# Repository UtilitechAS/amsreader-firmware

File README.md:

# AMS Reader
This code is designed to decode data from electric smart meters installed in many countries in Europe these days. The data is presented in a graphical web interface and can also send the data to a MQTT broker which makes it suitable for home automation project. Originally it was only designed to work with Norwegian meters, but has since been adapter to read any IEC-62056-7-5 or IEC-62056-21 compliant meters.

Later development have added Energy usage graph for both day and month, as well as future energy price. The code can run on any ESP8266 or ESP32 hardware which you can read more about in the [Wiki](https://wiki.amsleser.no/). If you don't have the knowledge to set up a ESP device yourself, or you would like to support our work, please have a look at our shop at [amsleser.no](https://www.amsleser.no/).

## Ready-made hardware

Pre-assembled readers running this firmware are available from [amsleser.no](https://www.amsleser.no/):

- **[Pow-K](https://www.amsleser.no/home/1-pow-k-han-port-reader-for-kamstrup-omnipower-meters.html)** – for Kamstrup Omnipower and 382M
- **[Pow-U](https://www.amsleser.no/home/7-pow-u-han-port-reader-for-m-bus-power-meters.html)** – for M-bus meters (HAN-NVE RJ45 in Norway/Sweden, RJ12 elsewhere)
- **[Pow-P1](https://www.amsleser.no/home/10-pow-p1-reader-for-power-meter-with-p1-port.html)** – for meters with P1 companion (DSMR) port

Not sure which one fits your meter? See the [Selection guide](https://www.amsleser.no/content/10-selection-guide).

## Installing pre-built firmware
If you have a device already running this firmware and you for some reason need to upgrade via USB port, you can use a [this web-based tool](https://www.amsleser.cloud/flasher)

If you are using a development board and want to flash a pre-built firmware manually, get the necessary files from the [release](https://github.com/UtilitechAS/amsreader-firmware/releases) section and visit the [WiKi](https://github.com/UtilitechAS/amsreader-firmware/wiki) and have a look at the [Flashing](   https://github.com/UtilitechAS/amsreader-firmware/wiki/flashing) section

## Building this project with PlatformIO
To build this project, you need [PlatformIO](https://platformio.org/) installed.

It is recommended to use Visual Studio Code with the PlatformIO plugin for development.

[Visual Studio Code](https://code.visualstudio.com/download)

[PlatformIO vscode plugin](https://platformio.org/install/ide?install=vscode)

For development purposes, copy the ```platformio-user.ini-example``` to ```platformio-user.ini``` and customize to your preference. The code will adapt to the platform and board set in your profile.

## Licensing
Initially, this project began as a hobby, consuming countless hours of our spare time. However, the time required to support this project has expanded beyond the scope of a hobby. As a result, we established ‘Utilitech’, a company dedicated to maintaining the software and hardware for this project as part of our regular work.

To ensure the sustainability of our venture, we have opted to license our software under the [Fair Source License] (https://fair.io). This approach allows the software to remain free for personal use, while also ensuring full transparency of our code’s inner workings. It also prevents competitors from exploiting our work without contributing to the maintenance of the code or providing technical support to end users.

For more information, please refer to our [LICENSE](/LICENSE) file.

If your usage falls outside the scope of this license and you require a separate license, please contact us at [post@utilitech.no](mailto:post@utilitech.no) for further details.

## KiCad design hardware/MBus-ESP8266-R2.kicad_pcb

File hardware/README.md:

[See Hardware page in Wiki](https://github.com/UtilitechAS/amsreader-firmware/wiki)

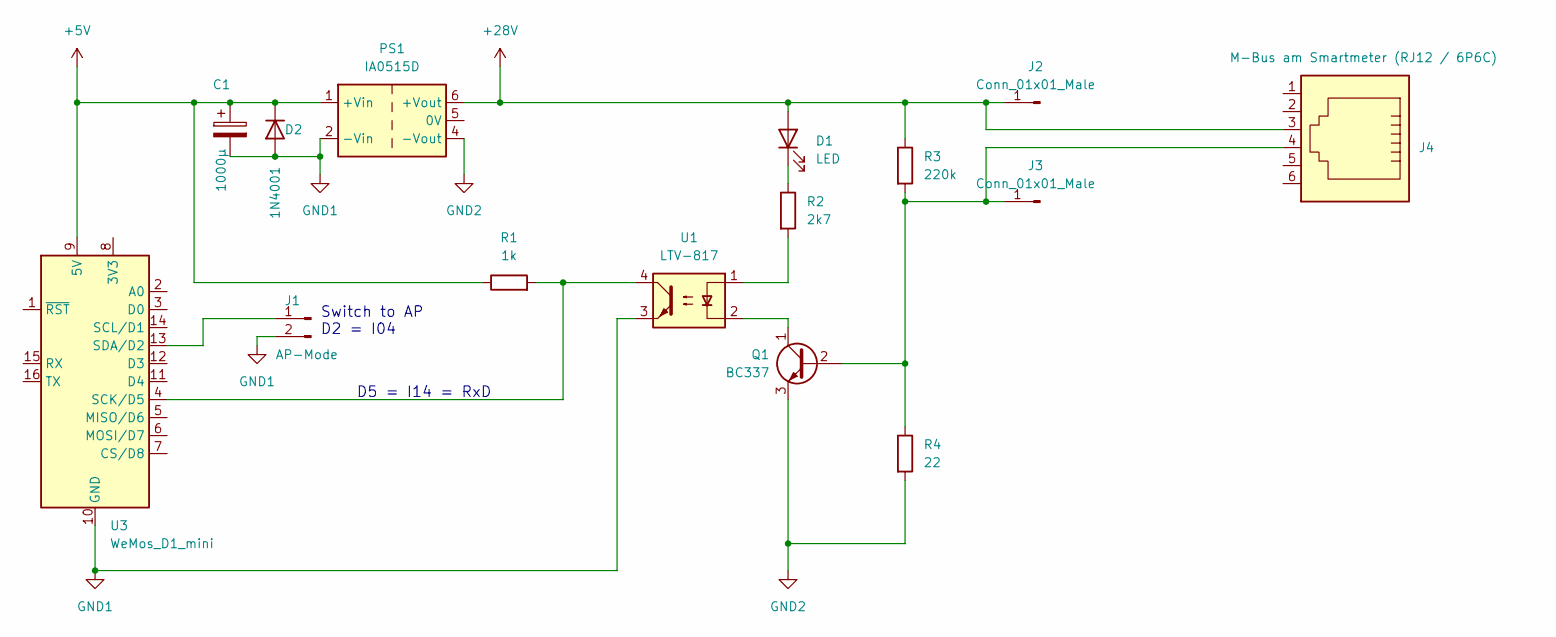
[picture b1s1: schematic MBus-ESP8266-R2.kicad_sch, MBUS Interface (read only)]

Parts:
C1: 1000µ; CP_Radial_D10.0mm_P5.00mm
D1: LED; LED_D3.0mm
D2: 1N4001; D_DO-41_SOD81_P10.16mm_Horizontal
J1: AP-Mode; PinHeader_1x02_P2.54mm_Vertical
J2, J3: Conn_01x01_Male; Pin_D1.0mm_L10.0mm
J4: M-Bus am Smartmeter (RJ12 / 6P6C); RJ12_Amphenol_54601
PS1: IA0515D; Converter_DCDC_XP_POWER-IAxxxxS_THT
Q1: BC337; TO-92_Inline_Wide
R1: 1k; R_Axial_DIN0207_L6.3mm_D2.5mm_P10.16mm_Horizontal
R2: 2k7; R_Axial_DIN0207_L6.3mm_D2.5mm_P10.16mm_Horizontal
R3: 220k; R_Axial_DIN0207_L6.3mm_D2.5mm_P10.16mm_Horizontal
R4: 22; R_Axial_DIN0207_L6.3mm_D2.5mm_P10.16mm_Horizontal
U1: LTV-817; DIP-4_W7.62mm
U3: WeMos_D1_mini; WEMOS_D1_mini_light

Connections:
+5V: C1.1, D2.1 (K), PS1.1 (+Vin), R1.1, U3.9 (5V)
+28V: D1.2 (A), J2.1, J4.3, PS1.6 (+Vout), R3.1
GND1: C1.2, D2.2 (A), J1.2, PS1.2 (-Vin), U1.3, U3.10 (GND)
GND2: PS1.4 (-Vout), Q1.3 (E), R4.2
unnamed: D1.1 (K), R2.1
unnamed: J1.1, U3.13 (SDA/D2)
unnamed: J3.1, J4.4, Q1.2 (B), R3.2, R4.1
unnamed: Q1.1 (C), U1.2
unnamed: R1.2, U1.4, U3.4 (SCK/D5)
unnamed: R2.2, U1.1

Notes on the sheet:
D5 = I14 = RxD
Switch to AP D2 = I04

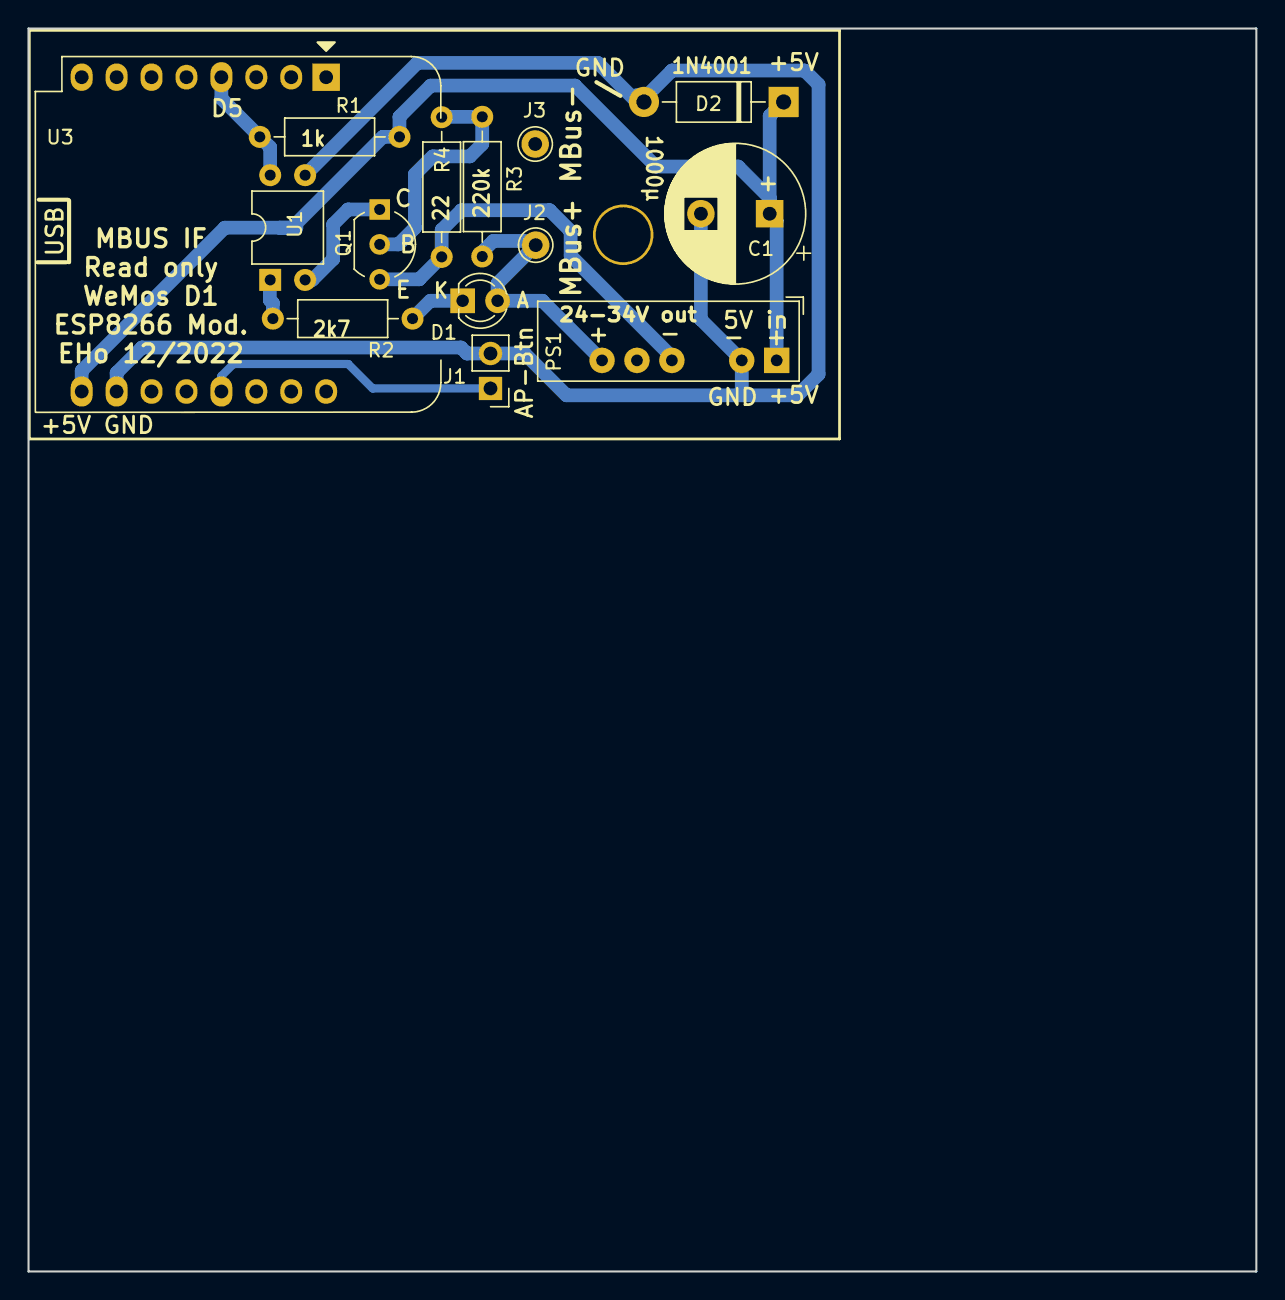
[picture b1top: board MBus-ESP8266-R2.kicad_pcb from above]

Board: 2 copper layers, 89.3 x 90.4 mm, 14 parts (0 on the bottom side), 10 nets.

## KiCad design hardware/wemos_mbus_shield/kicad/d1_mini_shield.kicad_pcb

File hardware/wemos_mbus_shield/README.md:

## Wemos shield

Fits D1 mini and S2 mini.

**WARNING** Not properly tested

**Resistors**
- R1:  470 (for U1)
- R2:  220 (for U1)
- R3:  82k (for U1)
- R4:  220 (for U1)
- R5: 100k (for U1)
- R6:  10k (for AP button)
- R7: 4.7k (for DS18B20)
- R8-R10: 1k (for RGB LED)

**Capacitors**
- C1: 100n (for U1)
- C2: 1u (for U1)
- C3: 100n (for U1)

**Other components**
- U1: TSS521 or TSS721
- U2: DS18B20 (Digital temperature sensor)
- D1: RGB LED
- J1: RJ45
- SW1: AP button (to D3 GPIO0)

**Jumper**
- JP1 & JP4: Jump these to receive power (5V) via RJ45 on pin 7 (GND) and 8 (+5)
- JP2 & JP3: Jump these to attach DS18B20 sensors via RJ45 on pin 4 (Data) and pin 5 (GND)

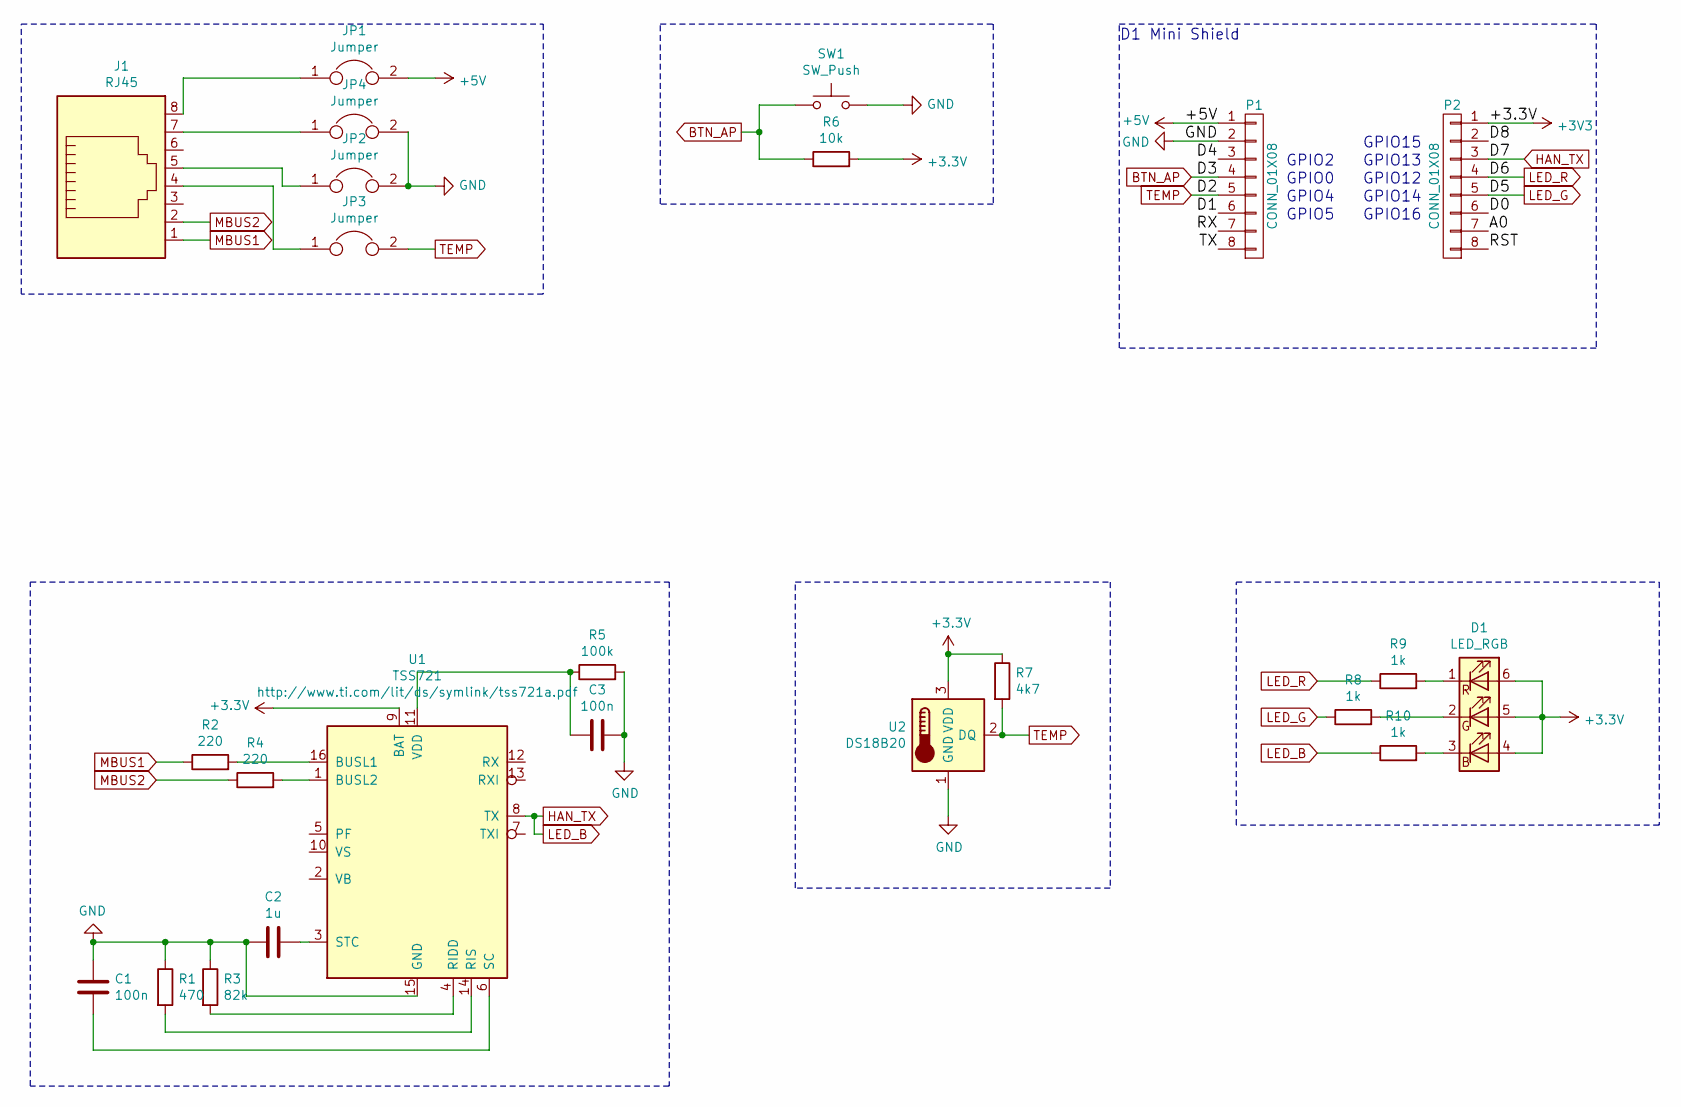
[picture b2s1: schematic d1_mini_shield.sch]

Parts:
C1, C3: 100n; R_0805_2012Metric_Pad1.15x1.40mm_HandSolder
C2: 1u; R_0805_2012Metric_Pad1.15x1.40mm_HandSolder
D1: LED_RGB; LED_RGB_PLCC-6
J1: RJ45; RJ45_Amphenol_54602-x08_Horizontal
JP1, JP2, JP3, JP4: Jumper; SolderJumper-2_P1.3mm_Open_RoundedPad1.0x1.5mm
P1, P2: CONN_01X08; D1_mini_Pin_Header
R1: 470; R_0805_2012Metric_Pad1.15x1.40mm_HandSolder
R2, R4: 220; R_0805_2012Metric_Pad1.15x1.40mm_HandSolder
R3: 82k; R_0805_2012Metric_Pad1.15x1.40mm_HandSolder
R5: 100k; R_0805_2012Metric_Pad1.15x1.40mm_HandSolder
R6: 10k; R_0805_2012Metric_Pad1.15x1.40mm_HandSolder
R7: 4k7; R_0805_2012Metric_Pad1.15x1.40mm_HandSolder
R8, R9, R10: 1k; R_0805_2012Metric_Pad1.15x1.40mm_HandSolder
SW1: SW_Push; SW_SPST_B3U-3000P
U1: TSS721; SOIC-16_3.9x9.9mm_P1.27mm
U2: DS18B20; TO-92_Inline

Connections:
+3V3: D1.4 (BA), D1.5 (GA), D1.6 (RA), P2.1, R6.2, R7.1, U1.9 (BAT), U2.3 (VDD)
+5V: JP1.2, P1.1
/A0: P2.7
/D0: P2.6
/D1: P1.6
/D4: P1.3
/D8: P2.2
/RST: P2.8
/RX: P1.7
/TX: P1.8
BTN_AP: P1.4, R6.1, SW1.1
GND: C1.1, C2.1, C3.2, JP2.2, JP4.2, P1.2, R1.1, R3.1, R5.2, SW1.2, U1.15 (GND), U2.1 (GND)
HAN_TX: P2.3, R10.1, U1.8 (TX)
LED_G: P2.5, R8.1
LED_R: P2.4, R9.1
MBUS1: J1.1, R2.1
MBUS2: J1.2, R4.1
unnamed: C1.2, U1.6 (SC)
unnamed: C2.2, U1.3 (STC)
unnamed: C3.1, R5.1, U1.11 (VDD)
unnamed: D1.1 (RK), R9.2
unnamed: D1.2 (GK), R8.2
unnamed: D1.3 (BK), R10.2
unnamed: J1.4, JP3.1
unnamed: J1.5, JP2.1
unnamed: J1.7, JP4.1
unnamed: J1.8, JP1.1
unnamed: R1.2, U1.14 (RIS)
unnamed: R2.2, U1.16 (BUSL1)
unnamed: R3.2, U1.4 (RIDD)
unnamed: R4.2, U1.1 (BUSL2)
TEMP: JP3.2, P1.5, R7.2, U2.2 (DQ)

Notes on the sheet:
GPIO2
GPIO0
GPIO4
GPIO5
GPIO15
GPIO13
GPIO12
GPIO14
GPIO16
D1 Mini Shield

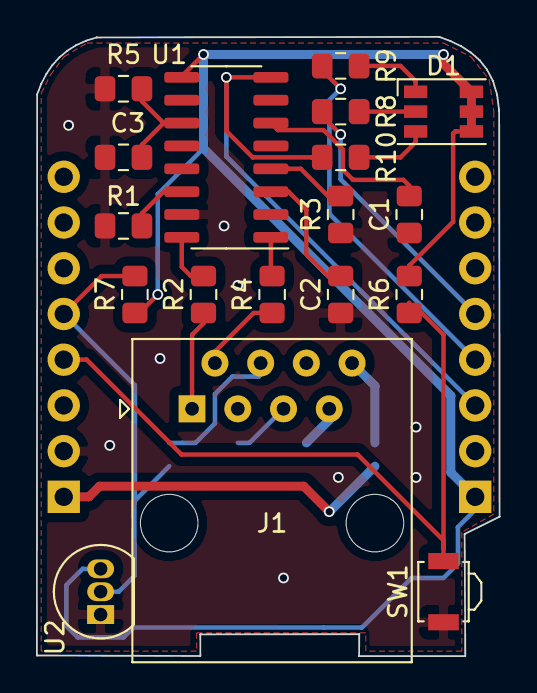
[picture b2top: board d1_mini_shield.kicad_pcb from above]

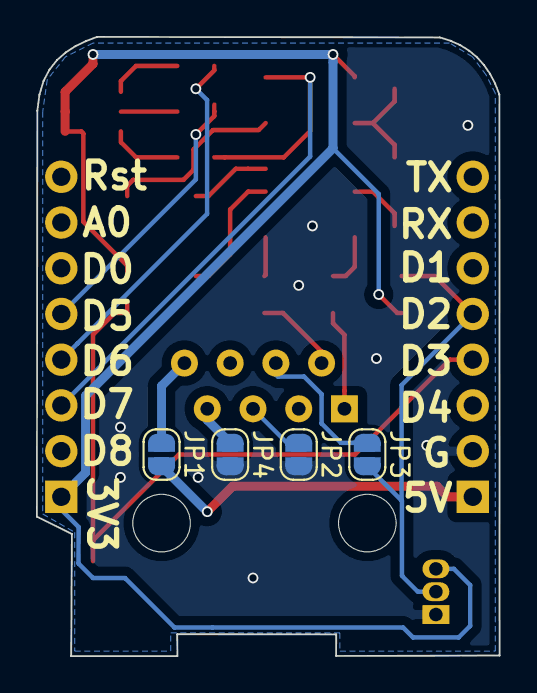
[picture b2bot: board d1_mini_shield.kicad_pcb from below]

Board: 2 copper layers, 25.7 x 34.4 mm, 24 parts (4 on the bottom side), 24 nets.

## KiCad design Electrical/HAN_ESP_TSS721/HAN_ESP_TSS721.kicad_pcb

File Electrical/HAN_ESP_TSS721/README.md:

# Electrical Design

## Explained
This design uses the [Texas Instruments TS721](http://www.ti.com/product/TSS721A) circuit for the M-bus to TTL conversion. From here, the 3.3V TTL signal is taken to the [ESP-12](http://www.esp8266.com/wiki/doku.php?id=esp8266-module-family#esp-12) / [ESP8266](http://esp8266.net/) for further processing and reporting over WiFi to MQTT. Really, this hardware is agnostic to what you choose to report to, the HAN library will help you decode the serial signal into readable meter values.

An addition to this design is using a DS18B20 as a temperature sensor. Just a little added value in monitoring the temperature of your fuse box.

There is an on-board programming option for the ESP. In order to do programming, my experience is that you'll be better off disconnecting the RX/TX from the TSS721, so there's two jumpers for this.

Other than this, it's all about software. You can find the [Arduino code](../../Code) to decode the HAN data and report the values over WiFi to an MQTT server.

## Schematics

## PCB

### Layers
| Top Copper | Bottom Copper | Silk | Combined |
| ---------- | ------------- | ---- | -------- |
|  |  |  |  |

## Source Code
The full KiCad source for these design files are here in this folder. Download this repository, start KiCad, chose open project and select HAN_ESP_TSS721.pro to get going.

## Componenet list
| Name | Value | Part | Comments |
| -----| ----- | ---- | -------- |
C1|220uF / 16V|[UVR1C221MED1TA](https://www.digikey.no/product-detail/en/nichicon/UVR1C221MED1TA/493-6096-1-ND/3438470)     | Electrolytic Capacitor |
C2|100nF / 63V         |[R82EC3100AA70J](https://www.digikey.no/product-detail/en/kemet/R82EC3100AA70J/399-5861-ND/2571296)           | Metal Film Capasitor |
C3|100nF / 63V         |[R82EC3100AA70J](https://www.digikey.no/product-detail/en/kemet/R82EC3100AA70J/399-5861-ND/2571296)           | Metal Film Capasitor |
C4|220uF / 16V|[UVR1C221MED1TA](https://www.digikey.no/product-detail/en/nichicon/UVR1C221MED1TA/493-6096-1-ND/3438470)     | Electrolytic Capacitor |
C5|220uF / 16V|[UVR1C221MED1TA](https://www.digikey.no/product-detail/en/nichicon/UVR1C221MED1TA/493-6096-1-ND/3438470)     | Electrolytic Capacitor |
C6|100nF / 63V         |[R82EC3100AA70J](https://www.digikey.no/product-detail/en/kemet/R82EC3100AA70J/399-5861-ND/2571296)           | Metal Film Capasitor |
R1 | 22k | [CF14JT22K0](https://www.digikey.no/product-detail/en/stackpole-electronics-inc/CF14JT22K0/CF14JT22K0CT-ND/1830383) | 0.25W resistor |
R2 | 470R | [CF14JT470R](https://www.digikey.no/product-detail/en/stackpole-electronics-inc/CF14JT470R/CF14JT470RCT-ND/1830342) | 0.25W resistor |
R3 | 10k | [CF14JT10K0](https://www.digikey.no/product-detail/en/stackpole-electronics-inc/CF14JT10K0/CF14JT10K0CT-ND/1830374) | 0.25W resistor |
R4 | 10k | [CF14JT10K0](https://www.digikey.no/product-detail/en/stackpole-electronics-inc/CF14JT10K0/CF14JT10K0CT-ND/1830374) | 0.25W resistor |
R5 | 10k | [CF14JT10K0](https://www.digikey.no/product-detail/en/stackpole-electronics-inc/CF14JT10K0/CF14JT10K0CT-ND/1830374) | 0.25W resistor |
R6 | 10k | [CF14JT10K0](https://www.digikey.no/product-detail/en/stackpole-electronics-inc/CF14JT10K0/CF14JT10K0CT-ND/1830374) | 0.25W resistor |
R7 | 10k | [CF14JT10K0](https://www.digikey.no/product-detail/en/stackpole-electronics-inc/CF14JT10K0/CF14JT10K0CT-ND/1830374) | 0.25W resistor |
R8 | 220R | [CF14JT220R](https://www.digikey.no/product-detail/en/stackpole-electronics-inc/CF14JT220R/CF14JT220RCT-ND/1830334) | 0.25W resistor |
R9 | 220R | [CF14JT220R](https://www.digikey.no/product-detail/en/stackpole-electronics-inc/CF14JT220R/CF14JT220RCT-ND/1830334) | 0.25W resistor |
R10 | 22k | [CF14JT22K0](https://www.digikey.no/product-detail/en/stackpole-electronics-inc/CF14JT22K0/CF14JT22K0CT-ND/1830383) | 0.25W resistor |
R11 | 4k7 | [CF14JT4K70](https://www.digikey.no/product-detail/en/stackpole-electronics-inc/CF14JT4K70/CF14JT4K70CT-ND/1830366) | 0.25W resistor |
U1 | TSS721 | [TSS721AD](https://www.digikey.no/product-detail/en/texas-instruments/TSS721AD/296-27127-5-ND/1910053) | M-bus tranciever |
U2 | ESP12-E | [ESP12](https://www.digikey.no/product-detail/en/adafruit-industries-llc/2491/1528-1438-ND/5761206) | ESP8266 SMT MODULE (Check e-bay for this one) |
U3 | LM1117-3.3 | [LD1117AS33TR](https://www.digikey.no/product-detail/en/LD1117AS33TR/497-1228-1-ND/586228) | 3.3V Voltage regulator |
U4 | DS18B20 | [DS18B20](https://www.digikey.no/product-detail/en/maxim-integrated/DS18B20/DS18B20-ND/420071) | Maxim Temp Sensor |
Q1 | BSS84 | [BSS84PH6433XTMA1](https://www.digikey.no/product-detail/en/BSS84PH6433XTMA1/BSS84PH6433XTMA1CT-ND/5410005) | P-FET transistor |
J1 | RJ45 | [54601-908WPLF](https://www.digikey.no/product-detail/en/amphenol-fci/54601-908WPLF/609-5081-ND/1488544)| RJ45 port
J2 | uUSB | [10118194-0001LF](https://www.digikey.no/product-detail/en/amphenol-fci/10118194-0001LF/609-4618-1-ND/2785382) | USB micro socket
J3 | 6-pin female header | [4320-01074-0](https://www.digikey.no/product-detail/en/murata-power-solutions-inc/4320-01074-0/811-2702-ND/2344918) | 6-pin female header
JP1 | | [XG8S-0241](https://www.digikey.no/product-detail/en/omron-electronics-inc-emc-div/XG8S-0241/Z5374-ND/4947394) | Jumper header
JP2 | | [XG8S-0241](https://www.digikey.no/product-detail/en/omron-electronics-inc-emc-div/XG8S-0241/Z5374-ND/4947394) | Jumper header
SW1 | Tactile Switch | [1825910-6](https://www.digikey.no/product-detail/en/te-connectivity-alcoswitch-switches/1825910-6/450-1650-ND/1632536) | Tactile Button
SW2 | Tactile Switch | [1825910-6](https://www.digikey.no/product-detail/en/te-connectivity-alcoswitch-switches/1825910-6/450-1650-ND/1632536) | Tactile Button
NONAME | | [STC02SYAN](https://www.digikey.no/product-detail/en/sullins-connector-solutions/STC02SYAN/S9000-ND/76372) | Unless you have these lying in your drawer, you'll need two

Complete shoppingcart, ready to order:
http://www.digikey.no/short/jj1vhv

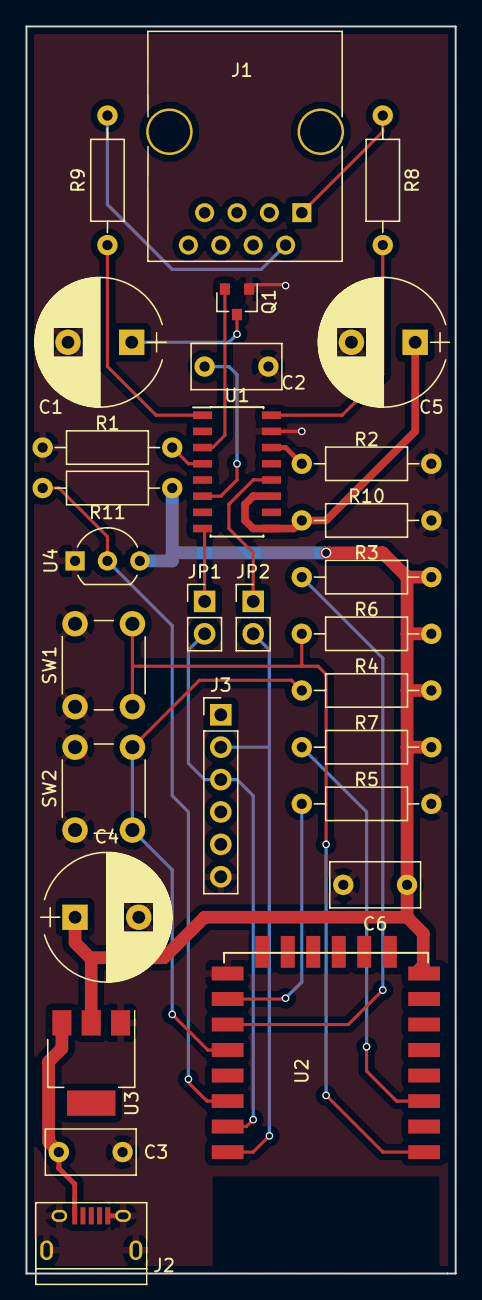
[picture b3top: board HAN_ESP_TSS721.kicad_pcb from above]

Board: 2 copper layers, 33.7 x 97.8 mm, 29 parts (0 on the bottom side), 23 nets.

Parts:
C1, C4, C5: 220u; CP_Radial_D10.0mm_P5.00mm
C2, C3, C6: 100n; C_Rect_L7.0mm_W3.5mm_P5.00mm
J1: RJ45; RJ45_8
J2: USB; USB_Micro-B
J3: FTDI; Pin_Header_Straight_1x06_Pitch2.54mm
JP1: RX; Pin_Header_Straight_1x02_Pitch2.54mm
JP2: TX; Pin_Header_Straight_1x02_Pitch2.54mm
Q1: BSS84; SOT-23
R1, R10: 22k; R_Axial_DIN0207_L6.3mm_D2.5mm_P10.16mm_Horizontal
R2: 470R; R_Axial_DIN0207_L6.3mm_D2.5mm_P10.16mm_Horizontal
R3, R4, R5, R6, R7: 10k; R_Axial_DIN0207_L6.3mm_D2.5mm_P10.16mm_Horizontal
R8, R9: 220R; R_Axial_DIN0207_L6.3mm_D2.5mm_P10.16mm_Horizontal
R11: 4k7; R_Axial_DIN0207_L6.3mm_D2.5mm_P10.16mm_Horizontal
SW1: ESP Reset; SW_PUSH_6mm_h5mm
SW2: ESP Prog; SW_PUSH_6mm_h5mm
U1: TSS721; SOIC-16_3.9x9.9mm_Pitch1.27mm
U2: ESP-12E; ESP-12E_SMD
U3: LM1117-3.3; SOT-223
U4: DS18B20; TO-92_Inline_Wide

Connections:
+3V3: C4.1, C6.1, R3.2, R4.1, R6.2, R7.1, R11.1, U2.8, U3.2, U4.3
ESP_PROG: R4.2, SW2.2, U2.12
ESP_RESET: R6.1, SW1.2, U2.1
ESP_RX: J3.3, JP1.2, U2.15
ESP_TX: J3.2, JP2.2, U2.16
ESP_Temp: R11.2, U2.14, U4.2
GND: C1.2, C2.2, C3.2, C4.2, C5.2, C6.2, J2.5, J2.6, J3.6, Q1.1, R1.2, R2.2, R5.1, R10.1, SW1.1, SW2.1, U1.15, U2.9, U3.1, U4.1
HAN_RX: JP2.1, U1.12
HAN_TX: JP1.1, U1.8
unnamed: C1.1, Q1.3
unnamed: C2.1, U1.6
unnamed: C3.1, J2.1, U3.3
unnamed: C5.1, R10.2, U1.9, U1.11
unnamed: J1.1, R8.1
unnamed: J1.2, R9.2
unnamed: Q1.2, U1.3
unnamed: R1.1, U1.4
unnamed: R2.1, U1.14
unnamed: R3.1, U2.11
unnamed: R5.2, U2.10
unnamed: R7.2, U2.3
unnamed: R8.2, U1.16
unnamed: R9.1, U1.1

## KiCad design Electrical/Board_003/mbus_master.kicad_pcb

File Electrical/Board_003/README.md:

# Overview

This board can be used to simulate a M-Bus master unit instead of
connecting to the real AMS unit, i.e. usable for test and development.
It takes a 5 V TTL level input (serial) signal and converts it
to a M-bus level signal. It only supports sending. Based on
[MBus_USB.pdf](https://github.com/rscada/libmbus/blob/master/hardware/MBus_USB.pdf)<sup>1</sup>.
It depends on an external power source capable of delivering 25-40 Volt.
Most DC-DC boost/step-up converter modules<sup>2</sup> should be fine for this.

## BOM

* D1 13V zener
* Q1-Q3 NPN transistor
* Q4 PNP transistor
* R1 1k
* R2 6.8k
* R3 1 (optional, can be shorted instead)
* R4 150
* R5 22k
* R6 220k

Note for the zener. This board depends on the zener to operate below 1mA,
e.g. like 1N5350 whereas a BZX55 will probably not operate properly.

This could be accomplished by reducing the 22k resistor so that it
draws enough current.

## Schematic

## PCB

-------------

<sup>1</sup>
See also https://electronics.stackexchange.com/questions/99388/designing-a-m-bus-master-up-to-10-slaves/ and https://electronics.stackexchange.com/a/214477/568.

<sup>2</sup>
Like for instance [this one](http://hobbycomponents.com/power/698-xl60009-dc-dc-step-up-boost-converter) for £3.

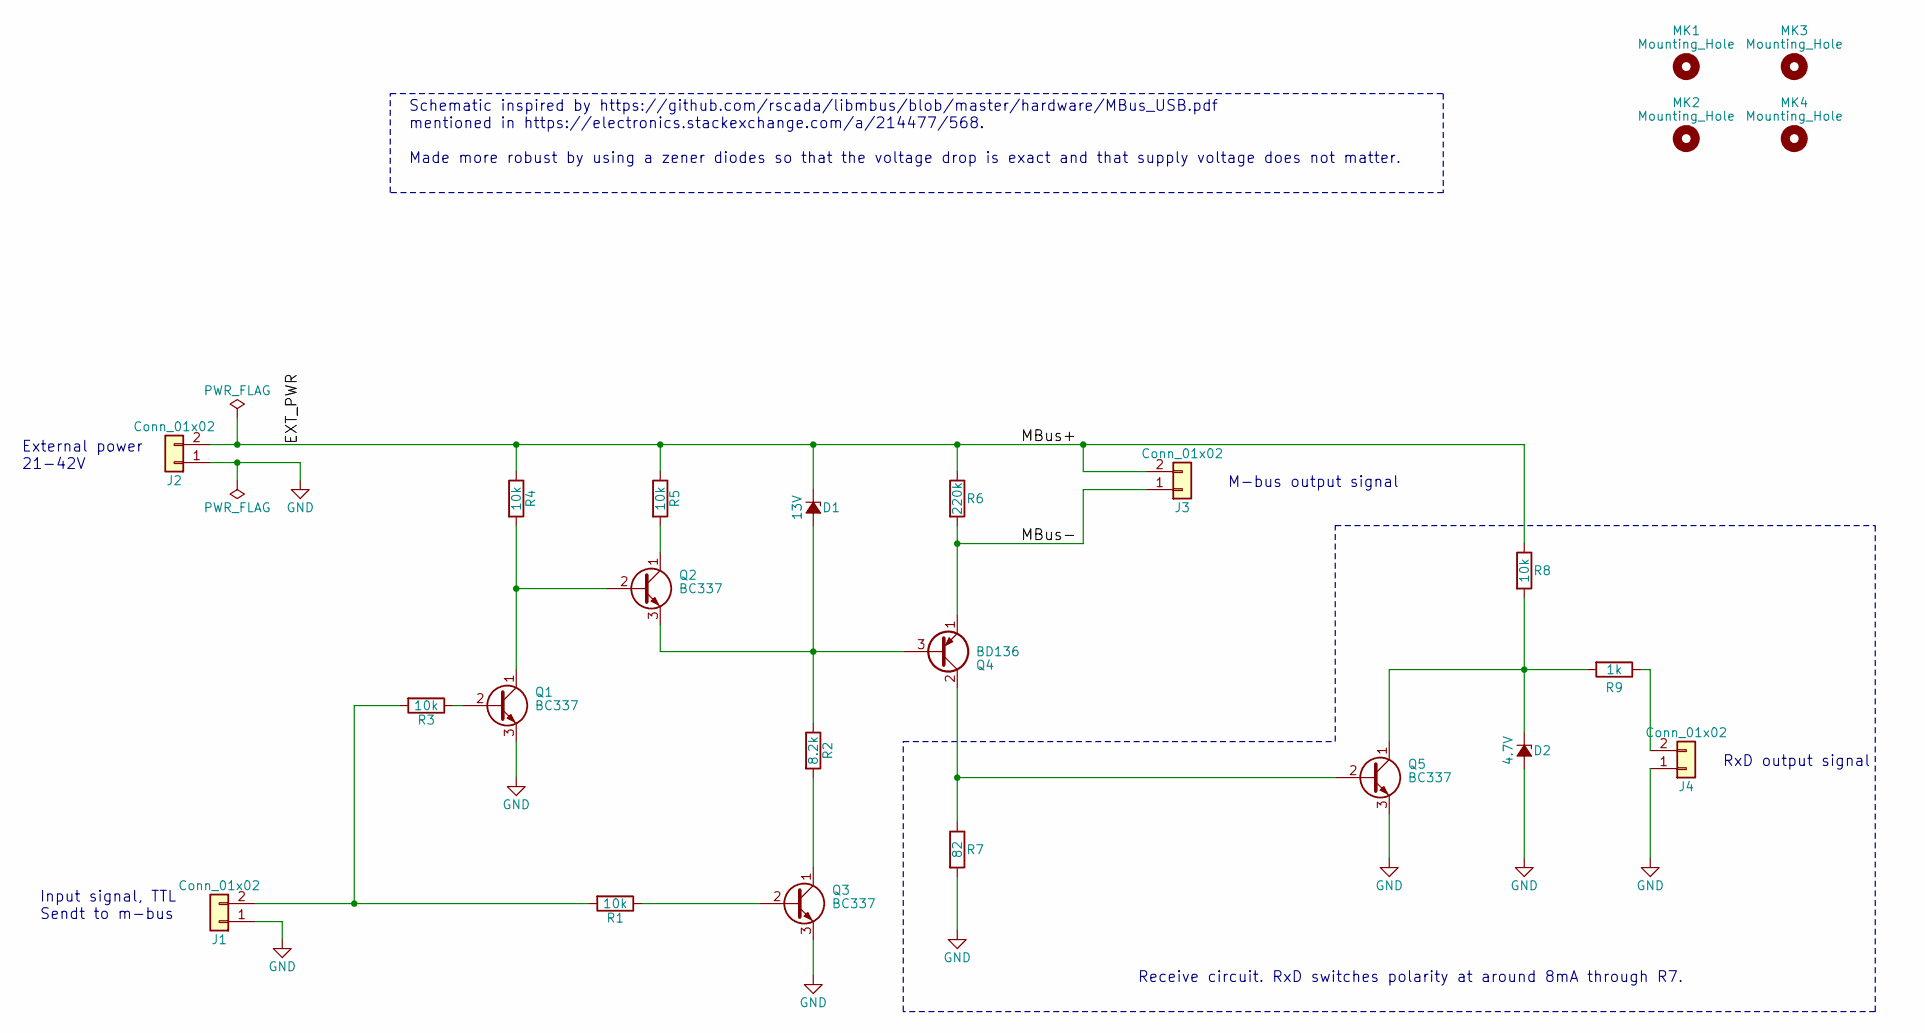
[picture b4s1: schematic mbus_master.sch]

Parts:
D1: 13V; D_5W_P12.70mm_Horizontal
D2: 4.7V; D_A-405_P7.62mm_Horizontal
J1, J2, J3, J4: Conn_01x02; Pin_Header_Straight_1x02_Pitch2.54mm
MK1, MK2, MK3, MK4: Mounting_Hole; MountingHole_4.3mm_M4_ISO14580
Q1, Q2, Q3, Q5: BC337; TO-92_Molded_Narrow
Q4: BD136; TO-126_Vertical
R1, R3, R4, R5, R8: 10k; R_Axial_DIN0207_L6.3mm_D2.5mm_P10.16mm_Horizontal
R2: 8.2k; R_Axial_DIN0207_L6.3mm_D2.5mm_P10.16mm_Horizontal
R6: 220k; R_Axial_DIN0207_L6.3mm_D2.5mm_P10.16mm_Horizontal
R7: 82; R_Axial_DIN0207_L6.3mm_D2.5mm_P10.16mm_Horizontal
R9: 1k; R_Axial_DIN0207_L6.3mm_D2.5mm_P10.16mm_Horizontal

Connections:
/EXT_PWR: D1.1 (K), J2.2, J3.2, R4.1, R5.1, R6.1, R8.1
/MBus-: J3.1, Q4.1 (E), R6.2
GND: D2.2 (A), J1.1, J2.1, J4.1, Q1.3 (E), Q3.3 (E), Q5.3 (E), R7.2
unnamed: D1.2 (A), Q2.3 (E), Q4.3 (B), R2.1
unnamed: D2.1 (K), Q5.1 (C), R8.2, R9.2
unnamed: J1.2, R1.2, R3.2
unnamed: J4.2, R9.1
unnamed: Q1.1 (C), Q2.2 (B), R4.2
unnamed: Q1.2 (B), R3.1
unnamed: Q2.1 (C), R5.2
unnamed: Q3.1 (C), R2.2
unnamed: Q3.2 (B), R1.1
unnamed: Q4.2 (C), Q5.2 (B), R7.1

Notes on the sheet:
External power 21-42V
Input signal, TTL Sendt to m-bus
M-bus output signal
Schematic inspired by https://github.com/rscada/libmbus/blob/master/hardware/MBus_USB.pdf mentioned in https://electronics.stackexchange.com/a/214477/568. Made more robust by using a zener diodes so that the voltage drop is exact and that supply voltage does not matter.
RxD output signal
Receive circuit. RxD switches polarity at around 8mA through R7.

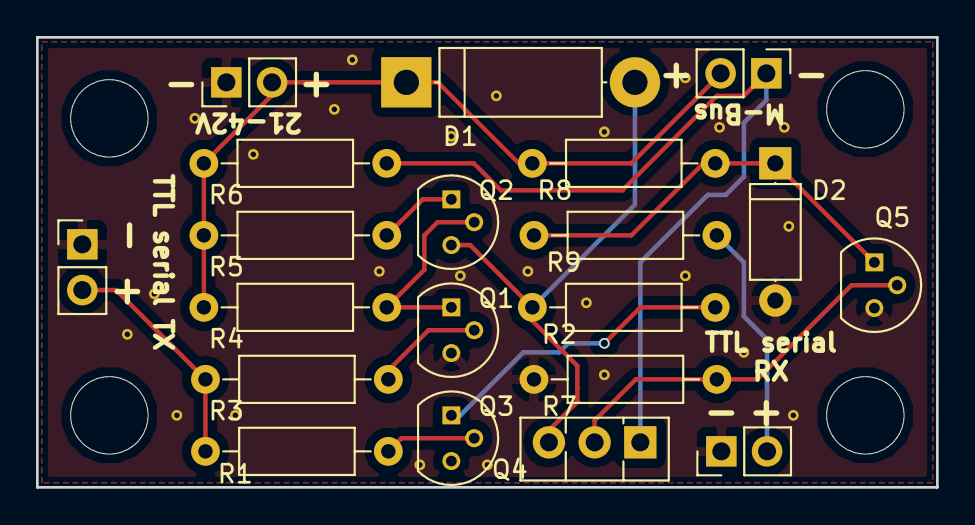
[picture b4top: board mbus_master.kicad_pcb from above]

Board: 2 copper layers, 50.0 x 25.0 mm, 24 parts (0 on the bottom side), 13 nets.

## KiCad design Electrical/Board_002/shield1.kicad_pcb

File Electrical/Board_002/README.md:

# Overview

This represents an alernative PCB for interfacing the HAN M-bus connector
on AMS meters.

The biggest difference between this board and [the original board](../Board_001)
is that this board supports communication over a physical wire.

So you can for instance use this board together with an arduino to make
a robust watt-meter display that will never fail because of connection
issues (unlike wifi).

This solution uses the industry standard chip for M-bus communication,
[TSS721A](http://www.ti.com/lit/ds/symlink/tss721a.pdf) with full
galvanic isolation to the bus, e.g. connecting a cable from this PCB
to a mains connected PC for instance will not result in a [ground
loop](https://en.wikipedia.org/wiki/Ground_loop_%28electricity%29).

The schematic and drawings are made with
[KiCad](http://www.kicad-pcb.org/).

# Scope

## Software

Reuse existing [code](../../Code).

## Hardware

Only support receiving transmitted serial data from the bus since the
Kamstrup AMS meters have no physical support for receiving anything.

The primary use case is to be a shield on an Arduino board (e.g. Uno or
Leonardo). A standalone ATtiny version would be nice to have as well.

Support daisy-chaining multiple units on the bus.

# Status

This is unfinished work, currently just started.

# Future

First phase is only supporting converting M-Bus data to serial I/O.
Support for ethernet or USB will be implicit via Arduino/shields. Later
standalone versions with ATTiny will be most useful by including
ethernet/usb support directly.

## Step 1

Create a simple M-Bus master simulator (transmit only) that takes
serial data and modulates onto the bus. Write arduino code to send a
test pattern and verify on oscilloscope.

https://electronics.stackexchange.com/questions/99388/designing-a-m-bus-master-up-to-10-slaves/99390#99390
https://electronics.stackexchange.com/a/214477/568

## Step 2

Connect the TSS721A chip with all required components with a optocoupler
between it and Arduino (e.g. M-Bus to TTL conversion). Connect with the
simulator from step 1 and verify that received data equals the data sendt.

Possibly also test with off-the-shelf M-Bus to TTL conversion hardware
for comparison.

## Step 3

Finish PCB design to be a usable Arduino shield. Integrate the
AmsToMqttBridge software. Display received data on LCD.

## Step 4

Put code onto ATTiny on a standalone board with support for either USB
or ethernet.

The MCP2221 is an inexpensive<sup>1</sup> USB to serial chip that people
[seems](https://www.element14.com/community/groups/open-source-hardware/blog/2016/02/01/implementing-non-ftdi-usb-to-uart-serial-interfaces)
[very](http://www.eevblog.com/forum/reviews/alternatives-to-ftdi-usb-to-uart-converter/)
[satisfied](https://hackaday.io/project/18845-usb-serial-uart)
[with](https://hackaday.com/2016/03/04/dual-uarti2c-breakout-goes-both-ways/).
It does [not](http://blog.zakkemble.co.uk/mcp2221-hid-library/)
[achieve](https://hackaday.com/2017/05/31/counterfeit-hardware-may-lead-to-malware-and-failure/#comment-3636318)
the maximum speeds is theoretically supports, but that is irrelevant for
this project. This board should then be powered by USB, both in that that
is the most natural and convinient choice and that if not then apparently
MCP2221 needs some additional electronics in order to [work properly as
an USB device](https://electronics.stackexchange.com/a/323551/568).

For ethernet the
[ENC28J60](http://www.microchip.com/wwwproducts/Devices.aspx?dDocName=en022889)
chip seems to be the
[go](https://www.reddit.com/r/arduino/comments/18pw59/diycheap_ethernet_shields/)
[to](https://www.open-electronics.org/low-cost-ethernet-shield-with-enc28j60/)
[solution](http://www.instructables.com/id/A-credit-card-sized-Ethernet-Arduino-compatable-co/)
[for](https://www.pocketmagic.net/atmega8-and-enc28j60-for-ethernet-support/)
[inexpensive](http://tuxgraphics.org/electronics/200606/article06061.shtml)<sup>2</sup>
DYI solutions. It only supports 10Mpbs, but that is more than
good engough for pushing out MQTT messages. It draws a significant
amount of current (~120mA or more) and gets gets hot so it might
need heatsinking, but that is an [inherent problem with all ethernet
controlles](https://electronics.stackexchange.com/questions/52349/why-is-ethernet-so-power-hungry).

-------------------

<sup>1</sup> Less than 20 NOK at [Elfa
Distrelec](https://www.elfadistrelec.no/en/interface-ic-uart-usb-so-14-microchip-mcp2221-sl/p/11087556),
cheaper elsewhere.

<sup>2</sup> 20-30 NOK for the
[chip](https://www.elfadistrelec.no/search?q=ENC28J60&filter_Category1=&filter_Category1=&filter_Category1=&filter_Category1=&filter_Category1=),
from 30-40 NOK for the
[connector](https://www.elfadistrelec.no/search?q=magjack&filter_Category1=&filter_Category1=&filter_Category1=&filter_Category1=&filter_Category1=&sort=Price:asc&page=1).

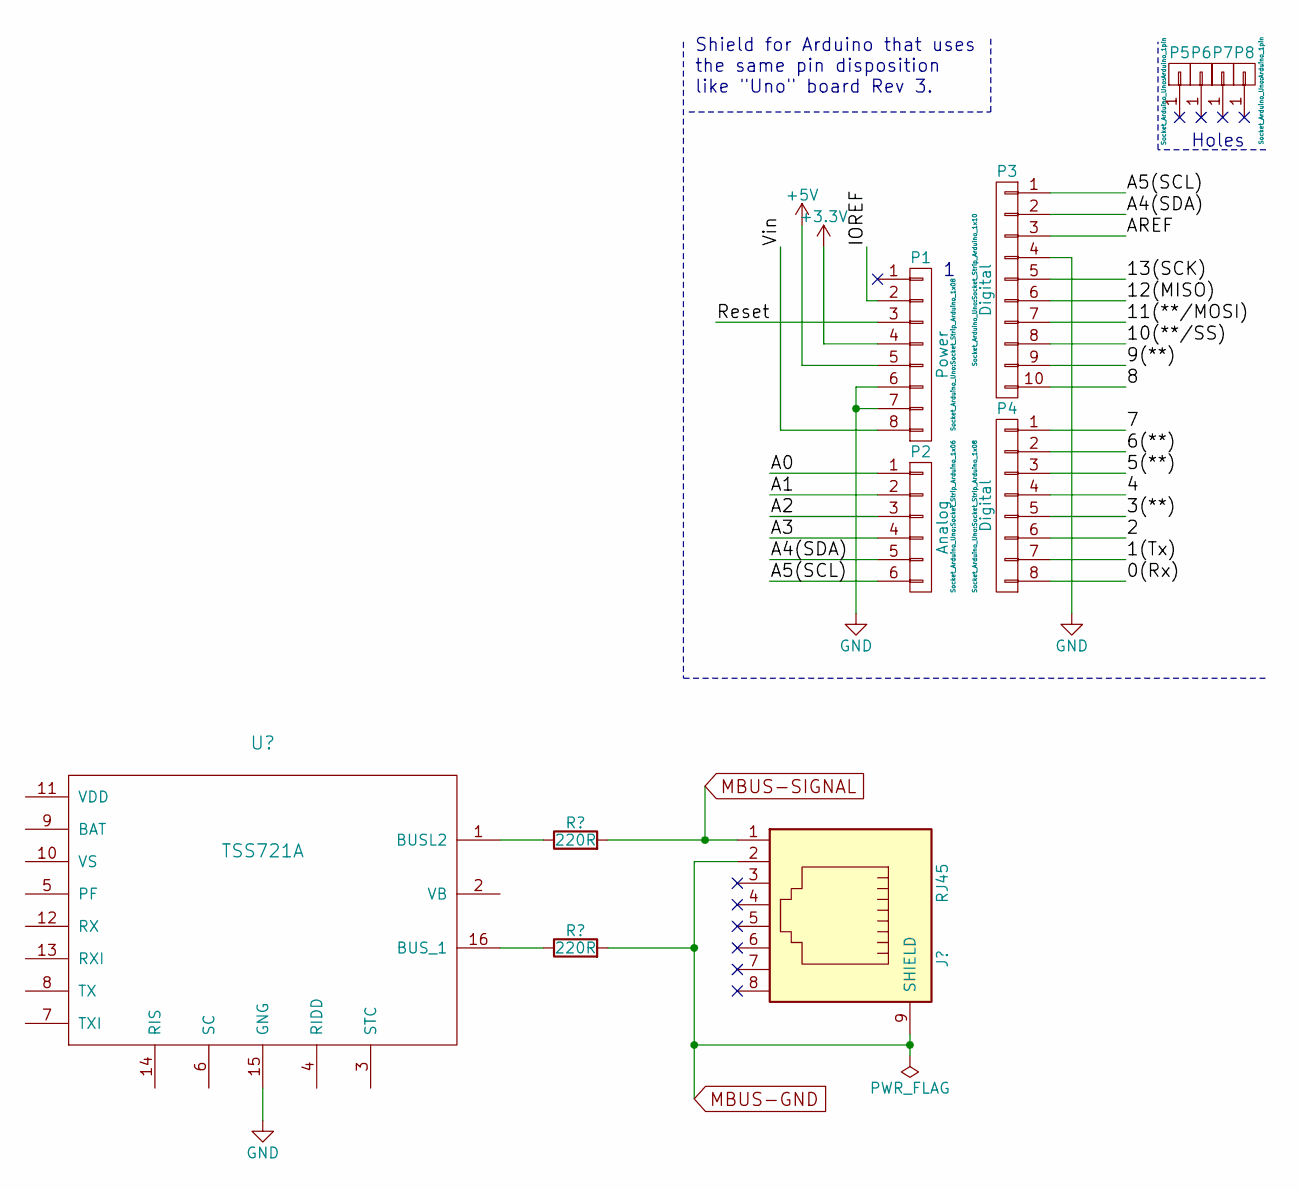
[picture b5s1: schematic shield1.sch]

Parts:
P1: Power; Socket_Strip_Arduino_1x08
P2: Analog; Socket_Strip_Arduino_1x06
P3: Digital; Socket_Strip_Arduino_1x10
P4: Digital; Socket_Strip_Arduino_1x08
P5, P6, P7, P8: CONN_01X01; Arduino_1pin

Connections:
+3V3: P1.4
+5V: P1.5
/0(Rx): P4.8
/1(Tx): P4.7
/2: P4.6
/3(**): P4.5
/4: P4.4
/5(**): P4.3
/6(**): P4.2
/7: P4.1
/8: P3.10
/9(**): P3.9
/10(**/SS): P3.8
/11(**/MOSI): P3.7
/12(MISO): P3.6
/13(SCK): P3.5
/A0: P2.1
/A1: P2.2
/A2: P2.3
/A3: P2.4
/A4(SDA): P2.5, P3.2
/A5(SCL): P2.6, P3.1
/AREF: P3.3
/IOREF: P1.2
/Reset: P1.3
/Vin: P1.8
GND: P1.6, P1.7, P3.4

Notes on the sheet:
Holes
Shield for Arduino that uses the same pin disposition like "Uno" board Rev 3.

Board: 2 copper layers, 8 parts (0 on the bottom side), 3 nets, no tracks yet.

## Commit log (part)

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2025-11-27 Fixed what hours the fixed price is applied to (#1069)
2025-11-27 Fixed default MQTT subscription (#1065)
2025-11-27 Re-added the memory leak fix
2025-11-27 Stop client before deleting
2025-12-01 Send raw data debug to MQTT
2025-12-01 Improve power stability when using MQTT (#1070)
    * Changes to improve MQTT and power stability
    * Re-added the memory leak fix
    * Re-added the memory leak fix
    * Stop client before deleting
    * Fixed potential nullpointer
2025-12-01 Sensor for /data, but it doesnt work
2025-12-01 Feature: Dump hex data from meter to MQTT (#1071)
    * Send raw data debug to MQTT
    * Publish hexdump to /data
    * Sensor for /data, but it doesnt work
2025-12-03 Temp removed meterid
2025-12-03 Fixed HDLC block decoding
2025-12-03 Changing some stuff back
2025-12-03 Change some stuff back
2025-12-05 Fixed reboot loop for some meters
2025-12-05 Fixed reboot loop for some meters (#1075)
2025-12-05 Changed MQTT client timeout setting for ESP8266 (#1077)
2025-12-09 Fixed building without remote debug (#1084)
2025-12-10 Fixed ESP8266 memory issue with price decoding
2025-12-10 Added compiled version
2025-12-10 Fixed float infinity issue
2025-12-10 Updated fix for non cet
2025-12-11 Fixed! I think...
2025-12-11 Disable auto buffer size for HAN on ESP8266 (#1086)
2025-12-11 Fixed ESP8266 memory issue with price decoding (#1089)
2025-12-29 Fixed extraction of negative prices from server
2025-12-29 Nullable timestamps for HA JSON
2025-12-29 Fixed IPv6 formatting
2025-12-29 Added debugging
2025-12-29 Added fake test frame
2025-12-29 Added support for frames without checksum
2025-12-30 Fixed IPv6 formatting (#1106)
2025-12-30 Fixed empty timestamp in Home-Assistant JSON (#1105)
    * Nullable timestamps for HA JSON
    * Nullable timestamps for MQTT JSON
2025-12-30 Added support for Iskraemeco IE.5 in Croatia (#1107)
    * Added support for Croation Iskra
    * Temp removed meterid
    * Fixed HDLC block decoding
    * Fixed context length
    * Changing some stuff back
    * Change some stuff back
2026-01-01 Fixed MQTT JSON for prices (#1116)
2026-01-08 If BUS powered, wait for capacitor to charge on boot, this ensures better boot stability
2026-01-08 Added support for a new format for a Iskra meter in Switzerland
2026-01-15 Fixed double slash on Wiki links
2026-02-05 Fixed decimal accuracy on saved values
2026-02-08 Add tariff counter support (Tariff 1 & 2) for import/export
2026-02-12 Added code to ensure stable boot (#1121)
    * If BUS powered, wait for capacitor to charge on boot, this ensures better boot stability
    * Some cleanup
2026-02-12 Fixed double slash on Wiki links (#1123)
2026-02-12 Fixed decimal accuracy on saved values (#1133)
2026-02-12 Fixed compile error for 8266 after #1121
2026-02-12 Allow for more errors during upgrade
2026-02-12 More instead of equals
2026-02-19 Use unique SSID on first boot
2026-02-26 Bump rollup from 3.29.5 to 3.30.0 in /lib/SvelteUi/app
    Bumps [rollup](https://github.com/rollup/rollup) from 3.29.5 to 3.30.0.
    - [Release notes](https://github.com/rollup/rollup/releases)
    - [Changelog](https://github.com/rollup/rollup/blob/v3.30.0/CHANGELOG.md)
    - [Commits](https://github.com/rollup/rollup/compare/v3.29.5...v3.30.0)
    ---
    updated-dependencies:
2026-02-26 Improved initial setup
2026-02-27 Moved reset of reboot reason to main program
2026-02-27 Allow up to 8 cycles to charge capacitor
2026-02-28 Bump svelte from 4.2.19 to 5.53.5 in /lib/SvelteUi/app
    Bumps [svelte](https://github.com/sveltejs/svelte/tree/HEAD/packages/svelte) from 4.2.19 to 5.53.5.
    - [Release notes](https://github.com/sveltejs/svelte/releases)
    - [Changelog](https://github.com/sveltejs/svelte/blob/main/packages/svelte/CHANGELOG.md)
    - [Commits](https://github.com/sveltejs/svelte/commits/svelte@5.53.5/packages/svelte)
    ---
    updated-dependencies:
2026-03-05 Bump svgo from 2.8.0 to 2.8.2 in /lib/SvelteUi/app
    Bumps [svgo](https://github.com/svg/svgo) from 2.8.0 to 2.8.2.
    - [Release notes](https://github.com/svg/svgo/releases)
    - [Commits](https://github.com/svg/svgo/compare/v2.8.0...v2.8.2)
    ---
    updated-dependencies:
    - dependency-name: svgo
2026-03-05 Improvements after testing
2026-03-05 Fixed parsing of Iskra
2026-03-05 Added PR workflow that creates a comment with firmware zip
2026-03-05 Fixed URL
2026-03-05 Bump svgo from 2.8.0 to 2.8.2 in /lib/SvelteUi/app (#1157)
    Bumps [svgo](https://github.com/svg/svgo) from 2.8.0 to 2.8.2.
    - [Release notes](https://github.com/svg/svgo/releases)
    - [Commits](https://github.com/svg/svgo/compare/v2.8.0...v2.8.2)
    ---
    updated-dependencies:
    - dependency-name: svgo
2026-03-05 Bump minimatch in /lib/SvelteUi/app (#1154)
    Bumps and [minimatch](https://github.com/isaacs/minimatch). These dependencies needed to be updated together.
    Updates `minimatch` from 9.0.5 to 9.0.9
    - [Changelog](https://github.com/isaacs/minimatch/blob/main/changelog.md)
    - [Commits](https://github.com/isaacs/minimatch/compare/v9.0.5...v9.0.9)
    Updates `minimatch` from 3.1.2 to 3.1.5
    - [Changelog](https://github.com/isaacs/minimatch/blob/main/changelog.md)
2026-03-05 Fixed incorrect color LED on boot (#1149)
2026-03-05 Initial changes to migrate to Svelte 5
2026-03-05 Updated node version in workflows
2026-03-05 Made proxy target configurable
2026-03-05 Added UI readme
2026-03-15 Fix issue for ex DLMS where accumulated is always included
2026-03-15 Added workflow to attach firmware in PR (#1160)
    * Added PR workflow that creates a comment with firmware zip
    * Fixed URL
    * Show version in comment
2026-03-15 Added .zip extension to avoid double zipping
2026-03-15 Fixed double zip
2026-03-19 Config via MQTT JSON payload
2026-03-20 Fixed ESP8266 build
2026-03-25 Bump picomatch from 2.3.1 to 2.3.2 in /lib/SvelteUi/app
    Bumps [picomatch](https://github.com/micromatch/picomatch) from 2.3.1 to 2.3.2.
    - [Release notes](https://github.com/micromatch/picomatch/releases)
    - [Changelog](https://github.com/micromatch/picomatch/blob/master/CHANGELOG.md)
    - [Commits](https://github.com/micromatch/picomatch/compare/2.3.1...2.3.2)
    ---
    updated-dependencies:
2026-03-26 Initial plan
2026-03-26 Continued implementation and changes after testing
2026-03-26 Fixed ESP8266 build errors
2026-04-08 Prevent boot loop if voltage is outside operating range
2026-04-08 Fixed code error
2026-04-09 Updated copyright
2026-04-09 Use unique SSID on first boot (#1143)
    * Use unique SSID on first boot
    * Debugger adjustments
2026-04-09 Moved reset of reboot reason to main program (#1153)
    * Moved reset of reboot reason to main program
    * Allow up to 8 cycles to charge capacitor
2026-04-09 Prevent boot loop in voltage check (#1171)
    * Prevent boot loop if voltage is outside operating range
    * Fixed code error
2026-04-09 Fixed price from config file reboot loop (#1172)
2026-04-09 Fixed voltage check
2026-04-09 Improved initial setup (#1148)
    * Improved initial setup
    * Improvements after testing
    * Adjustments after testing
    * Fixed ESP8266 build
    * Fixed voltage check
2026-04-09 Bump vite and @sveltejs/vite-plugin-svelte in /lib/SvelteUi/app
    Bumps [vite](https://github.com/vitejs/vite/tree/HEAD/packages/vite) and [@sveltejs/vite-plugin-svelte](https://github.com/sveltejs/vite-plugin-svelte/tree/HEAD/packages/vite-plugin-svelte). These de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
    Updates `vite` from 4.5.14 to 8.0.8
    - [Release notes](https://github.com/vitejs/vite/releases)
    - [Changelog](https://github.com/vitejs/vite/blob/main/packages/vite/CHANGELOG.md)
    - [Commits](https://github.com/vitejs/vite/commits/v8.0.8/packages/vite)
    Updates `@sveltejs/vite-plugin-svelte` from 2.5.3 to 7.0.0
2026-04-15 fix: capitalize voltage unit 'v' to 'V' in VoltPlot y-axis label
    Agent-Logs-Url: https://github.com/UtilitechAS/amsreader-firmware/sessions/742a66fe-8e10-467b-97c0-f54620131698
2026-05-15 Bump svelte from 4.2.19 to 5.55.7 in /lib/SvelteUi/app
    Bumps [svelte](https://github.com/sveltejs/svelte/tree/HEAD/packages/svelte) from 4.2.19 to 5.55.7.
    - [Release notes](https://github.com/sveltejs/svelte/releases)
    - [Changelog](https://github.com/sveltejs/svelte/blob/main/packages/svelte/CHANGELOG.md)
    - [Commits](https://github.com/sveltejs/svelte/commits/svelte@5.55.7/packages/svelte)
    ---
    updated-dependencies:
2026-05-17 Bump postcss from 8.5.2 to 8.5.14 in /lib/SvelteUi/app
    Bumps [postcss](https://github.com/postcss/postcss) from 8.5.2 to 8.5.14.
    - [Release notes](https://github.com/postcss/postcss/releases)
    - [Changelog](https://github.com/postcss/postcss/blob/main/CHANGELOG.md)
    - [Commits](https://github.com/postcss/postcss/compare/8.5.2...8.5.14)
    ---
    updated-dependencies:
2026-06-12 Extend tariff 1 & 2 counter coverage to DSMR and more DLMS paths (#1199)
    Follow-up to #1136: source Tariff 1 & 2 counters from DSMR (IEC6205621) and additional IEC6205675 (DLMS) paths; wire up the previously-unused T1/T2 OBIS constants.
2026-06-12 Added support for another Croatian Iskra (#1175)
    Adds another Iskra list format (similar to #1072/#1107, without reactive/power factor). Fixes #1174. Confirmed working by reporter @rivica-web.
2026-06-12 Fix lowercase voltage unit label in Voltage chart y-axis (#1179)
    Corrects the 230v y-axis tick label to 230V in VoltPlot.
2026-06-12 Updated CLAUDE.md
2026-06-12 Removed LF
2026-06-12 Restructure: flatten libs into src/, decoder into src/decoder/, UI into ui/ (#1200)
    Structural move: lib/* libraries flattened into src/, Arduino-free decoder into src/decoder/, Svelte app into ui/ (built at compile time). Build system unified (scripts/generate_includes.py); CI buil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
2026-06-12 Add esp32s2psram dev target with mbedTLS PSRAM override
    Tasmota's prebuilt mbedTLS sets CONFIG_MBEDTLS_INTERNAL_MEM_ALLOC=1,
    which forces every TLS allocation into internal SRAM and ignores
    PSRAM even when it's available. Override the calloc/free hooks at
    runtime so SSL record buffers and BIGNUM workspace land in PSRAM,
    freeing ~40 KB of internal heap during an active TLS session.
    The override is gated by both the BOARD_HAS_PSRAM compile flag and
2026-06-12 Non-blocking LED flashing with slow error codes and meter-LED suppression (#1201)
    Non-blocking ledFlash/ledLoop state machine; slow countable error codes, fast other blinks, meter-LED suppression during error bursts.
2026-06-12 Add esp32s2psram dev target with mbedTLS PSRAM override (#1202)
    Adds esp32s2psram build env for ESP32-S2 boards with PSRAM, incl. mbedTLS PSRAM allocation override.
2026-06-12 Add compile-time custom MQTT connector via custom/ overlay (#1204)
    Optional compile-time custom MQTT connector enabled via the custom/ overlay (CUSTOM_MQTT_* defines). Build unchanged when overlay absent.
2026-06-12 Add services status tile, header indicator, and Localazy source pipeline (#1205)
    Per-service status tile on the status page, header services badge colored by worst state, and the Localazy source-of-truth pipeline (localazy/source/en.json). Custom MQTT row wired now that #1204 is 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
2026-06-30 Bump vite and @sveltejs/vite-plugin-svelte in /ui
    Bumps [vite](https://github.com/vitejs/vite/tree/HEAD/packages/vite) and [@sveltejs/vite-plugin-svelte](https://github.com/sveltejs/vite-plugin-svelte/tree/HEAD/packages/vite-plugin-svelte). These de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
    Updates `vite` from 6.4.2 to 8.1.1
    - [Release notes](https://github.com/vitejs/vite/releases)
    - [Changelog](https://github.com/vitejs/vite/blob/main/packages/vite/CHANGELOG.md)
    - [Commits](https://github.com/vitejs/vite/commits/v8.1.1/packages/vite)
    Updates `@sveltejs/vite-plugin-svelte` from 5.1.1 to 7.1.2
